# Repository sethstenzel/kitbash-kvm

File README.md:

# KitBash KVM
KitBash KVM is a hardware and software solution for controlling one machine with another.

If you have ever wanted a simple device to let you control another machine with your current screen, mouse, and keyboard, be that a server, raspberry pi, or android device, KitBash KVM lets you do that, and is 100% open source.

KitBash KVM let's you use your laptop screen, mouse, and keyboard on another machine.

## Where to Buy?
I will be keeping built devices and kits on my tindie store.

## How to use?
Plug in a USBC cable to your laptop, and then one USBC cable and one HDMI cable to the machine you wish to control.
Next choose to either use the installationless Web Controller at [controller.kitbashkvm.com](https://controller.kitbashkvm.com) in Google Chrome or Microsoft Edge, or download a native Windows client from the Microsoft Store.

See the [User Guide](docs/wiki.md) for how to use the controller, and [BUILD.md](BUILD.md) to build it yourself.

## Can I make my own?
ABSOLUTELY! Wiki instructions here on GitHub will detail how to build or use alternative parts.
You can also visit the DIY page on KitBashKVM.com for more details and assembly videos.

## Can I get a custom color case?
If you purchase a DIY kit reach out to me and we can see what we can do.

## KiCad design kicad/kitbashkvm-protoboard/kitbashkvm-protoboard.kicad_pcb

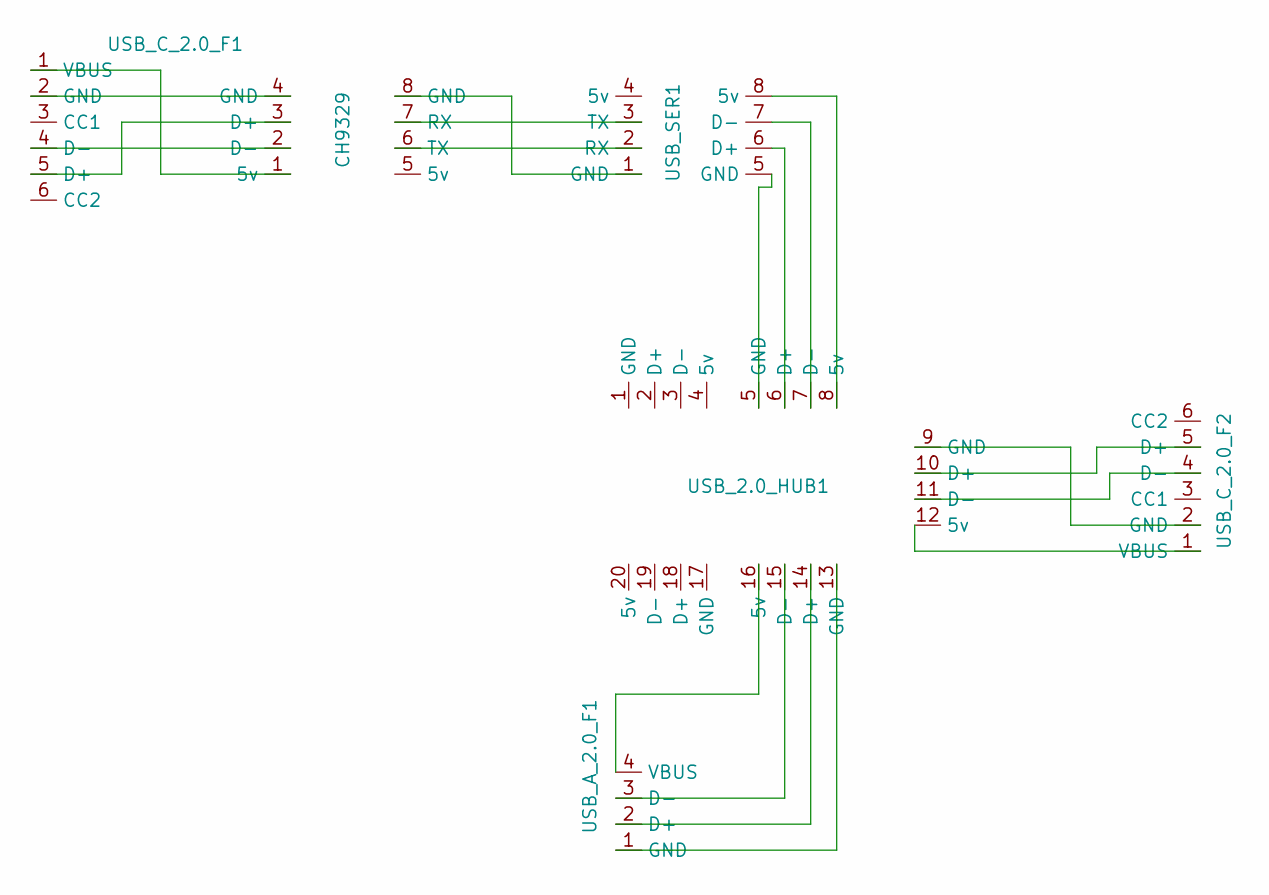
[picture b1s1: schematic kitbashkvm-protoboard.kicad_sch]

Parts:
CH9329: CH9329_UART_TO_USB_2.0
USB_2.0_HUB1: USB_2.0_HUB
USB_A_2.0_F1: USB_A_2.0_F
USB_C_2.0_F1, USB_C_2.0_F2: USB_C_2.0_F
USB_SER1: CH340_TO_USB_2.0

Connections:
unnamed: CH9329.3 (D+), USB_C_2.0_F1.5 (D+)
unnamed: CH9329.2 (D-), USB_C_2.0_F1.4 (D-)
unnamed: CH9329.8 (GND), USB_SER1.1 (GND)
unnamed: CH9329.7 (RX), USB_SER1.3 (TX)
unnamed: CH9329.6 (TX), USB_SER1.2 (RX)
unnamed: USB_2.0_HUB1.8 (5v), USB_SER1.8 (5v)
unnamed: USB_2.0_HUB1.5 (GND), USB_SER1.5 (GND)
unnamed: USB_2.0_HUB1.14 (D+), USB_A_2.0_F1.2 (D+)
unnamed: USB_2.0_HUB1.15 (D-), USB_A_2.0_F1.3 (D-)
unnamed: USB_2.0_HUB1.13 (GND), USB_A_2.0_F1.1 (GND)
unnamed: USB_2.0_HUB1.16 (5v), USB_A_2.0_F1.4 (VBUS)
unnamed: CH9329.4 (GND), USB_C_2.0_F1.2 (GND)
unnamed: CH9329.1 (5v), USB_C_2.0_F1.1 (VBUS)
unnamed: USB_2.0_HUB1.10 (D+), USB_C_2.0_F2.5 (D+)
unnamed: USB_2.0_HUB1.11 (D-), USB_C_2.0_F2.4 (D-)
unnamed: USB_2.0_HUB1.9 (GND), USB_C_2.0_F2.2 (GND)
unnamed: USB_2.0_HUB1.12 (5v), USB_C_2.0_F2.1 (VBUS)
unnamed: USB_2.0_HUB1.6 (D+), USB_SER1.6 (D+)
unnamed: USB_2.0_HUB1.7 (D-), USB_SER1.7 (D-)

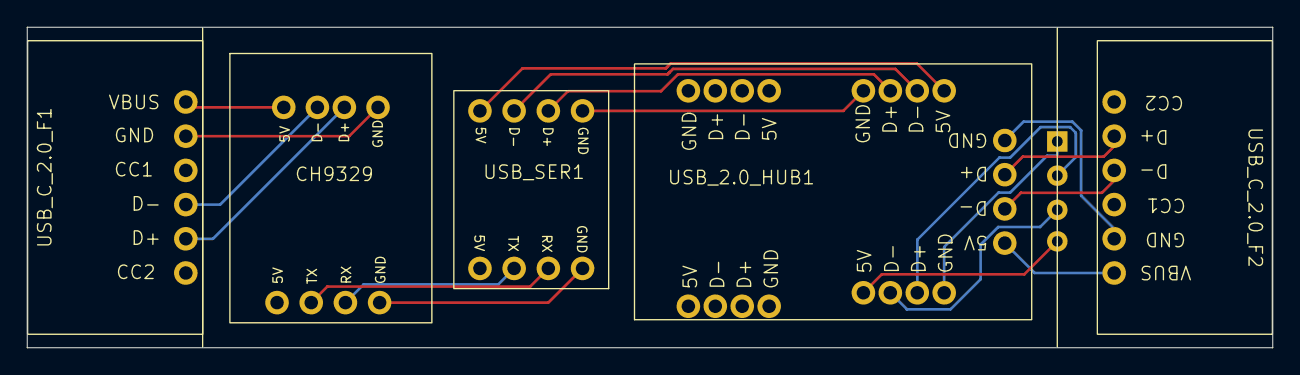
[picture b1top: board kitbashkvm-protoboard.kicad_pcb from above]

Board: 2 copper layers, 92.5 x 23.8 mm, 6 parts (1 on the bottom side), 19 nets.

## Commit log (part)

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2025-12-24 Initial push to github.
2025-12-24 added kicad folder / project
2025-12-29 added draw.io wireup image
2026-01-09 kicad files and updated gitignore
2026-01-09 added new baud settings after testing sipeed nanokvm usb, and fixed tauri build issue.
